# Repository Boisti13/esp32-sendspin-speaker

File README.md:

# ESP32 Sendspin Speaker

A network speaker for Home Assistant and Music Assistant on an ESP32-A1S
audio board. It plays [Sendspin](https://www.sendspin-audio.com/) streams
(Music Assistant's synchronised multi-room audio), shows what's playing on a
small colour screen and has hardware buttons for play/pause, volume and
tracks. Built with ESPHome.

> Since v0.2.0 it uses the Sendspin components built into ESPHome 2026.10;
> no pull requests or external components any more.

## Highlights

- **Sendspin player**: shows up in Music Assistant as a player and plays in
  sync with other Sendspin speakers.
- **ES8388 codec** on the A1S board, stereo, 48 kHz / 32-bit I²S; output
  set to both outputs (speaker and headphone) at boot, on the device itself.
- **Amplifier switched with playback**: on 150 ms after playback starts
  (no pop while the codec settles), off 300 ms after it stops or pauses (no
  click on the last audio).
- **1.47" screen** (320 × 172 landscape, ST7789V): play/pause icon, volume,
  IP address, title and artist. Long names end in "...", accented letters
  (ä, ö, ü, ß, é) are in the font. Redrawn only when something changes.
- **Rides out Wi-Fi gaps**: 2.5 MB of audio buffered ahead in PSRAM
  (Sendspin's default is 1 MB, about 5 s).
- **Diagnostics in Home Assistant**: Wi-Fi signal, uptime, free PSRAM and
  heap, and the reason for the last restart. A signal worse than about −70 dBm means dropouts: move the speaker
  or the access point, or use a board with an external antenna.
- **Five buttons that work without Home Assistant**: play/pause, previous,
  next, volume down/up go straight to the player and on to Music Assistant
  through Sendspin. Headphone jack detection.
- **Play picks up where you left off**: with nothing playing, even right
  after power-on, button 1 asks Music Assistant to play, and it resumes
  the speaker's queue with the last track.
- **Chime when it's online**: a short three-note chime when Wi-Fi first
  connects after power-on (not on later reconnects, and not over music).
  Built into the firmware. *Boot Sound* in Home Assistant turns it off;
  the setting survives restarts.

## Hardware

| Part | |
|---|---|
| Board | ESP32-A1S audio kit (ESP32-WROVER with PSRAM, ES8388 codec) |
| Codec | ES8388, I²C SDA 33 / SCL 32; I²S LRCLK 25, BCLK 27, DOUT 26, MCLK 0 |
| Amplifier enable | GPIO21 |
| Screen | Waveshare 1.47" 172 × 320, ST7789V; SPI CLK 14, MOSI 13, CS 15, DC 22, RST 12 |
| Headphone jack detect | GPIO39 |

### Buttons

| Button | Pin | Does | Entity in Home Assistant |
|---|---|---|---|
| 1 | GPIO36 | pause; when not playing, play (resumes Music Assistant's queue) | *Button 1 Play/Pause* |
| 2 | — | its pin (GPIO13) is the screen's MOSI | — |
| 3 | GPIO19 | previous track | *Button 3 Previous Track* |
| 4 | GPIO23 | next track | *Button 4 Next Track* |
| 5 | GPIO18 | volume down | *Button 5 Volume Down* |
| 6 | GPIO5 | volume up | *Button 6 Volume Up* |

The numbers are the ones printed on the board (KEY1–KEY6).

GPIO12 (screen reset) is a strapping pin: if it is high at power-on the
ESP32 picks 1.8 V flash and doesn't boot. Worth moving if boot is flaky.

### Custom PCB (in design)

A battery-powered board set of its own is being designed in KiCad in
[`hardware/`](hardware/README.md): a main board with the same ESP32-A1S
module, two 3 W amplifiers, a 1S LiPo charger and one USB-C port for
charging and flashing; a front panel with the screen (SPI like this one,
or an I²C OLED) and the buttons; a small USB-C board. Panel, USB-C,
battery, speakers, status LED, on/off switch and charge LEDs connect by
JST cable. It keeps the pins above, screen included, so it will get its
own `speaker-diy.yaml` with few changes. Not built yet.

## Install

| Step | |
|---|---|
| 1 | Copy `secrets.example.yaml` to `secrets.yaml` and fill in Wi-Fi, a new API key (`openssl rand -base64 32`) and an OTA password. In Home Assistant's ESPHome app the shared `secrets.yaml` gets `speaker_1_key` and `speaker_1_ota_password`. |
| 2 | Put `speaker.yaml`, `fonts/` and `sounds/` into the ESPHome folder. |
| 3 | Flash once over USB: `esphome run speaker.yaml`. After that, over Wi-Fi. |
| 4 | Add the device in Home Assistant with the API key. It needs no Home Assistant actions. |
| 5 | In Music Assistant, enable the Sendspin provider; the speaker appears as a player. |

## Example: playing an album

Start an album in Music Assistant on *Sendspin Media Player*. The board
switches to *playing*, waits 150 ms, turns the amplifier on and two seconds
later draws the screen once: pause icon, `VOL 65%`, the title in large type
and the artist below (*Die Ärzte* shows with its umlaut; a long title ends
in "..."). Press button 6 and the volume goes up a step; the screen redraws
with the new value. Press button 4 and Music Assistant skips to the next track.
Press button 1 to pause: the icon changes to play and the amplifier turns off
300 ms later.

## Layout

```
speaker.yaml           the whole device: board, codec, Sendspin, screen, buttons
requirements.txt       the ESPHome version it is tested with
fonts/                 Ubuntu Medium and Material Design Icons for the screen
sounds/boot.wav        the boot chime (1.5 s, 22 kHz mono)
scripts/make-boot-sound.py  makes sounds/boot.wav (synthesised, MIT like the rest)
secrets.example.yaml   the secrets the config expects
hardware/              KiCad 10 projects for the custom PCBs: main, front panel, USB-C (CERN-OHL-P-2.0)
```

## Development

- Check a change: `esphome config speaker.yaml`, then
  `esphome compile speaker.yaml`.
- ESPHome **2026.10.0** (`requirements.txt`), the version of Home
  Assistant's ESPHome app. Sendspin, `speaker_source` and `media_source`
  are built in since then; older versions don't have them.
- The screen has `update_interval: never`: every change that shows on it
  calls `component.update: tft_display`.
- Another boot sound: replace `sounds/boot.wav` (WAV, MP3, FLAC or Opus,
  short, ideally with ~300 ms of silence in front so the amplifier is on
  when it starts) or change and run `scripts/make-boot-sound.py`.

## License

MIT, see [LICENSE](LICENSE). The hardware in `hardware/` is under
CERN-OHL-P-2.0, see [hardware/LICENSE](hardware/LICENSE). Fonts: see
[THIRD_PARTY_NOTICES.md](THIRD_PARTY_NOTICES.md).

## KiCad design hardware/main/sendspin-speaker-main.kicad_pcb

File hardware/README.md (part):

# Custom PCB — Rev A (in design)

A battery-powered board set for the Sendspin speaker, replacing the
ESP32-Audio-Kit. It keeps the Audio Kit's pins wherever it can — the SPI
screen even stays on the same pins — so the firmware carries over as
`speaker-diy.yaml` with only the battery, charge and LED parts added.
KiCad 10 projects; the hardware is licensed under CERN-OHL-P-2.0
([LICENSE](LICENSE)), the firmware in the repo root under MIT.

> Status: all schematics drawn (ERC clean). **Main board placed, routed
> (Freerouting) and labelled**, DRC without errors, JLC files can be made.
> Front panel and USB-C board placed, not routed yet. Before ordering: check
> the NS4150B values and the part rotations (see *Open checks*). Nothing
> built or tested.

| Main board, 70 × 60 mm | Front panel, 75 × 45 mm | USB-C board, 32 × 22 mm |
|---|---|---|
|  |  |  |

Reference designators are numbered per sheet: MCU 1xx, Power 2xx, USB 3xx,
Audio 4xx, Connectors 5xx (front panel and USB-C board: 6xx, 7xx).

## Highlights

- **Three boards**: the main board with module, audio and power; a front
  panel with the display and the five buttons; a small USB-C board.
  Everything that sits in the enclosure wall — panel, USB-C, battery,
  speakers, status LED, on/off switch, charge LEDs — connects by JST cable,
  so the main board can go anywhere in the case.
- **USB-C either way**: on the main board directly, or on the USB-C board
  through a cable. Both footprints are on the main board; fit one.
- **SPI or I²C display**: the panel connector carries SCK/SCL, MOSI/SDA, CS
  and DC, so it takes the ST7789 the Audio Kit build uses (same pins), or
  an SSD1306/SH1106 OLED on the first two lines.
- **ESP32-A1S (Ai-Thinker, ES8388 version)**, the same module as the Audio
  Kit, hand-soldered (JLC doesn't stock it). Antenna over the board edge or
  a cutout; the footprint carries a copper keepout under it.
- **Stereo, 2 × 3 W**: two NS4150B in BTL into 4 Ω, powered straight from
  the battery, enabled together on GPIO21.
- **1S LiPo** with TP4056 charging (~500 mA, so any PC port works),
  DW01A + FS8205A protection, load sharing, red/green charge LEDs that the
  firmware can read too.
- **One USB-C port** for charging and flashing (CH340C with auto-reset).
- **On/off switch after the charger**: the battery still charges while the
  speaker is off.
- **0805 wherever possible** for resistors, capacitors and LEDs, so
  everything can be hand-soldered and reworked.

## Boards

| Board | KiCad project | Carries |
|---|---|---|
| Main | [`main/`](main/) | ESP32-A1S, amps, charger and protection, regulators, CH340C, Boot/Reset, on-board options for switch and charge LEDs, all connectors below |
| Front panel | [`ui/`](ui/) | buttons 1, 3, 4, 5, 6 and headers only (SPI and I²C display, status LED): any panel wiring can replace it |
| USB-C | [`usb/`](usb/) | USB-C receptacle only: any USB-C breakout or panel socket can replace it |

## Connectors (main board)

JST XH (2.5 mm) unless noted. Pin 1 first.

| Ref | To | Pins | Signals |
|---|---|---|---|
| J_UI | front panel | XH 12 | 3V3, GND, SCK/SCL (14), MOSI/SDA (13), CS (15), DC (22), BTN1 (36), BTN3 (19), BTN4 (23), BTN5 (18), BTN6 (5), LED (12, through R501 330 Ω) |
| J_USB | USB-C board | XH 6 | VBUS, D−, D+, CC1, CC2, GND |
| USB1 | — | USB-C 16-pin | the on-board option, in parallel with J_USB |
| J_BAT | LiPo cell | XH 2 | BAT+, BAT− |
| J_SW | on/off switch | XH 2 | VBAT_LS, VBAT_SW (switch in series) |
| J_CHG | charge LEDs | XH 3 | LED+ (VBUS), CHRG (red cathode), STDBY (green cathode) |
| J_LED | status LED | XH 3 | VBAT_SW, LED (12) through 330 Ω, GND |
| J_SPK_L | left speaker | XH 2 | OUTP, OUTN |
| J_SPK_R | right speaker | XH 2 | OUTP, OUTN |

- **Speakers are bridged (BTL)**: neither wire is ground. Never tie a
  speaker wire to GND or share a return between the two speakers.
- **Battery on JST XH** like every other cable: most cells ship with a PH
  plug, so crimp an XH plug on (or use an adapter lead). Cells differ in
  polarity: check before plugging in. Silkscreen `+`/`−` at the connector.
- **J_UI**: a SPI display uses all four display lines; an I²C OLED only
  SCK/SCL and MOSI/SDA, with the two 4.7 kΩ pull-ups on the main board
  fitted (leave them off for SPI). GPIO36's 10 kΩ pull-up is on the main
  board too, so the panel has nothing but buttons to GND and headers.
  Keep the cable short (≤ 20 cm). The LED pin is GPIO12 after R501
  (330 Ω), so a panel LED wires straight on.
- **J_USB / USB1**: the 5.1 kΩ CC resistors (R301/R302) and the USBLC6-2SC6
  are on the main board and serve both, so the off-board side is a bare
  receptacle: our USB-C board or any breakout that brings out VBUS, D−, D+,
  CC1, CC2 and GND (leave R301/R302 off if it has its own 5.1 kΩ). Fit
  either USB1 or J_USB, not both. The cable carries charge and
  load current (amps on battery through load sharing), so XH's 3 A per pin
  is plenty; keep it short (≤ 15 cm) for USB full speed.
- **J_SW**: the switch goes in series between load sharing and VBAT_SW.
  Fit either the on-board MSK12C02 or J_SW with a panel switch; with
  neither, bridge the solder jumper next to them.
- **J_CHG**: the LED resistors stay on the main board; the on-board 0805
  LEDs are in parallel and can be left off.
- **J_LED**: GPIO12 goes out through R501 (330 Ω), so a plain LED wires
  straight to LED/GND; VBAT_SW is there for an SK6812-type LED (needs
  > 3.7 V, hence not 3V3; R501 is its data series resistor). The on-board
  LED (D101/R108) stays as well.

## Parts and footprints

Footprints are set on the symbol the moment it is placed. KiCad's own
library where it has the part; otherwise imported from LCSC into
`lib/lcsc` (see [Libraries](#libraries)).

| Block | Part | Footprint | LCSC |
|---|---|---|---|
| Module | ESP32-A1S (ES8388), hand-soldered | `lcsc:WIRELM-SMD_ESP32-A1S` (+ antenna keepout) | C277945 |
| Amps | 2 × NS4150B | `lcsc:MSOP-8_L3.0-W3.0-P0.65-LS5.0-BL` | C189961 |
| Bulk | 470 µF, ≥ 6.3 V | `Capacitor_SMD:CP_Elec_8x10` | |
| Charger | TP4056 | `Package_SO:SOIC-8-1EP_3.9x4.9mm_P1.27mm_EP2.41x3.3mm` | |
| Protection | DW01A | `Package_TO_SOT_SMD:SOT-23-6` | |
| | FS8205A | `lcsc:SOT-23-6_L2.9-W1.6-P0.95-LS2.8-BR` | C2830320 |
| Load sharing | AO3401A | `Package_TO_SOT_SMD:SOT-23` | |
| | SS34 | `Diode_SMD:D_SMA` | |
| Power switch | MSK12C02 | `lcsc:SW-TH_MSK12C02` | C431540 |
| Switch bypass | solder jumper JP201 | `Jumper:SolderJumper-2_P1.3mm_Open_RoundedPad1.0x1.5mm` | |
| Charge status | 2 × BAT54W (GPIO isolation) | `Package_TO_SOT_SMD:SOT-323_SC-70` | |
| 3.3 V | AP2112K-3.3 | `Package_TO_SOT_SMD:SOT-23-5` | |
| 3.3 V (CH340C) | XC6206P332MR | `Package_TO_SOT_SMD:SOT-23-3` | |
| USB-UART | CH340C | `Package_SO:SOIC-16_3.9x9.9mm_P1.27mm` | |
| Auto-reset | UMH3N | `Package_TO_SOT_SMD:SOT-363_SC-70-6` | |
| ESD | USBLC6-2SC6 | `Package_TO_SOT_SMD:SOT-23-6` | |
| USB-C | 16-pin receptacle | `Connector_USB:USB_C_Receptacle_HRO_TYPE-C-31-M-12` | |
| Boot, Reset | tactile 5.1 × 5.1 mm | `Button_Switch_SMD:SW_Push_1P1T_XKB_TS-1187A` | |
| Panel buttons | tactile 6 × 6 mm THT | `Button_Switch_THT:SW_PUSH_6mm` | |
| Display headers | 1 × 8 (SPI), 1 × 4 (I²C) | `Connector_PinHeader_2.54mm:PinHeader_1x08/1x04_P2.54mm_Vertical` | |
| JST XH | B*B-XH-A vertical | `Connector_JST:JST_XH_B<n>B-XH-A_1x<n>_P2.50mm_Vertical` | |
| R, C, LED | | `Resistor_SMD:R_0805_2012Metric`, `Capacitor_SMD:C_0805_2012Metric`, `LED_SMD:LED_0805_2012Metric` | |

LCSC numbers for the KiCad-library parts are filled in when they go into
the schematic (field `LCSC`), for JLC assembly.

**0805** for resistors, capacitors and LEDs wherever the part exists in
it. Exceptions: the bulk capacitor, and values that don't come in 0805 at
the needed voltage (check 22 µF for ≥ 10 V rating and DC-bias derating).

**Values and wiring notes**

- TP4056: R_PROG 2.4 kΩ (~500 mA). CHRG/STDBY reach GPIO4/GPIO2 through
  BAT54W diodes (cathode at the TP4056): the LEDs hang off VBUS, and without
  the diodes 5 V would leak into the GPIOs — and GPIO2 high at reset would
  stop USB flashing.
- CH340C: own XC6206 3.3 V from VBUS (USB only, no battery drain), V3 tied
  to VCC, TX/RX through 470 Ω. Auto-reset DTR/RTS → EN/GPIO0; EN 10 kΩ
  pull-up + 1 µF. GPIO0 is also the codec's MCLK, as on the Audio Kit.
- USB-C: 5.1 kΩ on CC1 and CC2 separately; A6/B6 and A7/B7 tied.
- Module: 22 µF + 100 nF at 3V3.
- NS4150B: inputs from the module's differential speaker outputs through
  100 nF + 100 kΩ per leg (gain = 240 kΩ / Rin = 2.4, −3 dB at 16 Hz; 47 kΩ
  gives 5.1 if it's too quiet), Bypass 1 µF, supply 10 µF + 1 µF (the
  datasheet's 1 µF instead of 100 nF), R421 100 kΩ pull-down on AMP_EN so
  the amps stay off while booting.
- No headphone output (owner, 2026-10-30): the module's HPOUTL/R are left
  open; GPIO39 (the Audio Kit's headphone detect) keeps its 10 kΩ pull-up
  and is spare.
- Front panel: no parts besides buttons and headers. ST7789 RST tied to
  3.3 V (the driver sends a software reset), backlight always on; J604
  takes a status LED directly.
- Battery sense: 2 × 470 kΩ + 100 nF on the **cell** (VBAT) → GPIO34, ~4.5 µA.
  Not on VBAT_SW: with USB in, load sharing puts ~4.6 V from VBUS there and
  the cell couldn't be measured while charging.
- Protection sits in the negative lead: BAT_N is the cell's minus, GND
  the protected system ground (P−). DW01A: 100 Ω / 100 nF supply, CS via 1 kΩ.
- Load sharing: SS34 from VBUS to the load (VBAT_LS); AO3401A with drain
  at the cell, source at the load, gate on VBUS (100 kΩ to GND), so it
  connects the cell only without USB.
- AP2112K-3.3: 10 µF in and out, EN tied to VIN.
- Flashing over USB needs the switch on.

## Open checks

- **NS4150B values**: Rin/Cin from the gain formula; the typical
  application page of the datasheet wasn't readable either — compare.
- **Part rotations** in JLC's placement preview: KiCad and JLC disagree on
  some footprints' zero orientation (SOT-23, SOIC, USB-C).

## Pin plan

The ESP32-A1S keeps the codec's I²C (GPIO32/33) and I²S (25/26/27/35)
inside the module; they are not on its pads. The free pads are GPIO 0, 2,
4, 5, 12, 13, 14, 15, 18, 19, 21, 22, 23, 34, 36, 39 and TX/RX.

| Function | GPIO | Same as Audio Kit? |
|---|---|---|
| Codec I²C / I²S | 32/33, 25/26/27/35 + MCLK 0 | yes, inside the module |
| Display SCK/SCL, MOSI/SDA, CS, DC | 14, 13, 15, 22 | yes (the ST7789's pins; its reset on 12 is dropped) |
| Amp enable | 21 | yes |
| Buttons 1 play/pause, 3 prev, 4 next, 5 vol −, 6 vol + | 36, 19, 23, 18, 5 | yes; 36 needs an external 10 kΩ pull-up |
| Spare (was headphone detect) | 39 | 10 kΩ pull-up kept; input only |
| Status LED | 12 | new; 10 kΩ pull-down keeps the strap low at boot |
| CHRG / STDBY | 4 / 2 | new; through BAT54W, internal pull-ups |
| Battery ADC | 34 | new |
| UART (CH340C) | 1 / 3 | yes |

Strapping pins: GPIO12 must be low at reset (else 1.8 V flash, no boot),
GPIO2 low or floating for USB flashing, GPIO15 high (CS's pull-up keeps it
so). All pads are in use.

## Firmware changes (`speaker-diy.yaml`, later)

- Display: keep the ST7789 config without `reset_pin`, or switch to
  `ssd1306_i2c` with `i2c: sda: 13, scl: 14` (a second bus; the codec's
  stays on 33/32) and a monochrome UI.
- Battery `adc` on GPIO34 (12 dB, ×2, cell voltage); warn below 3.5 V (LDO).
- Status LED on GPIO12.
- *Charging* / *Charged* binary sensors on GPIO4/GPIO2 (pull-up): charging =
  CHRG low and STDBY high, charged = STDBY low and CHRG high; anything else
  means no USB (without VBUS both can read low through the TP4056).

## Libraries

- KiCad 10's standard libraries for everything they have.
- `lib/lcsc.*`: the five parts KiCad doesn't have, imported from LCSC's
  EasyEDA library with [easyeda2kicad](https://github.com/uPesy/easyeda2kicad.py)
  (symbol, footprint, STEP model). Afterwards: 3D paths point at
  `${KIPRJMOD}/../lib/lcsc.3dshapes/`, the locating pegs of MSK12C02 and
  PJ-320D are non-plated, the A1S got an antenna keepout and a courtyard
  around its pads, the PJ-320D a courtyard (it had none) and its 3D model
  moved 7.6 mm onto its pads, and MSK12C02 is marked SMD. Check every
  imported part's courtyard and 3D model before using it.
  See [THIRD_PARTY_NOTICES.md](../THIRD_PARTY_NOTICES.md).
- `lib/sendspin-speaker.*`: parts we draw ourselves (none yet).

To import another part: `easyeda2kicad --full --lcsc_id C… --output
<scratch>/lcsc`, check it, then merge it into `lib/lcsc.*` with the same
fixes.

## Layout

```
main/sendspin-speaker-main.kicad_*   main board; the top sheet is the block diagram
main/usb.kicad_sch                   USB-C, ESD, CH340C, auto-reset
main/power.kicad_sch                 charger, protection, load sharing, switch, 3V3, battery sense
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
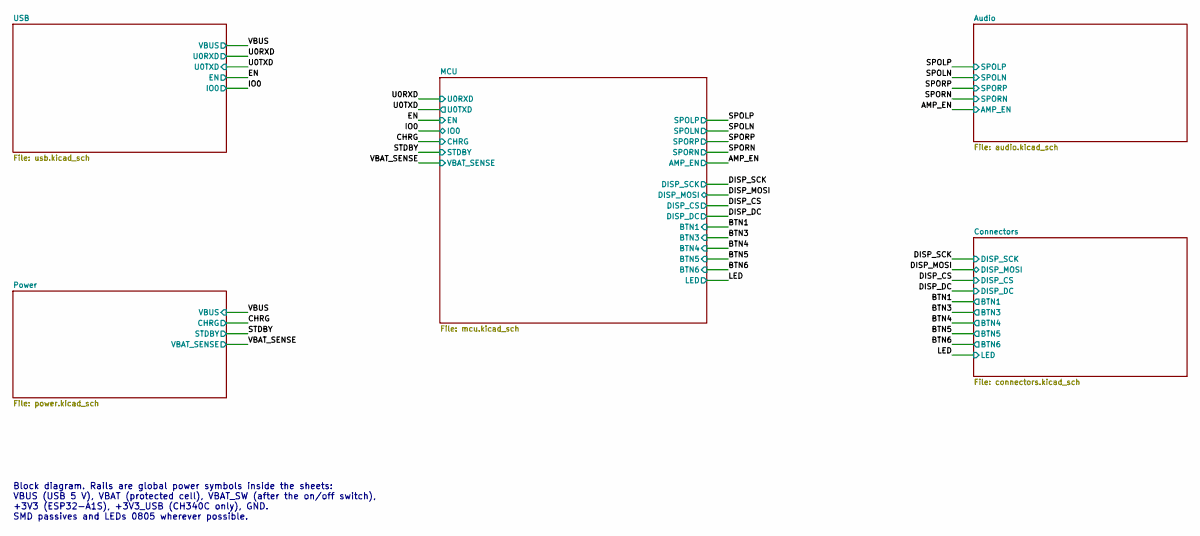
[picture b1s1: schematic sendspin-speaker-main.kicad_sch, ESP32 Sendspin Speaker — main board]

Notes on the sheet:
Block diagram. Rails are global power symbols inside the sheets: VBUS (USB 5 V), VBAT (protected cell), VBAT_SW (after the on/off switch), +3V3 (ESP32-A1S), +3V3_USB (CH340C only), GND. SMD passives and LEDs 0805 wherever possible.

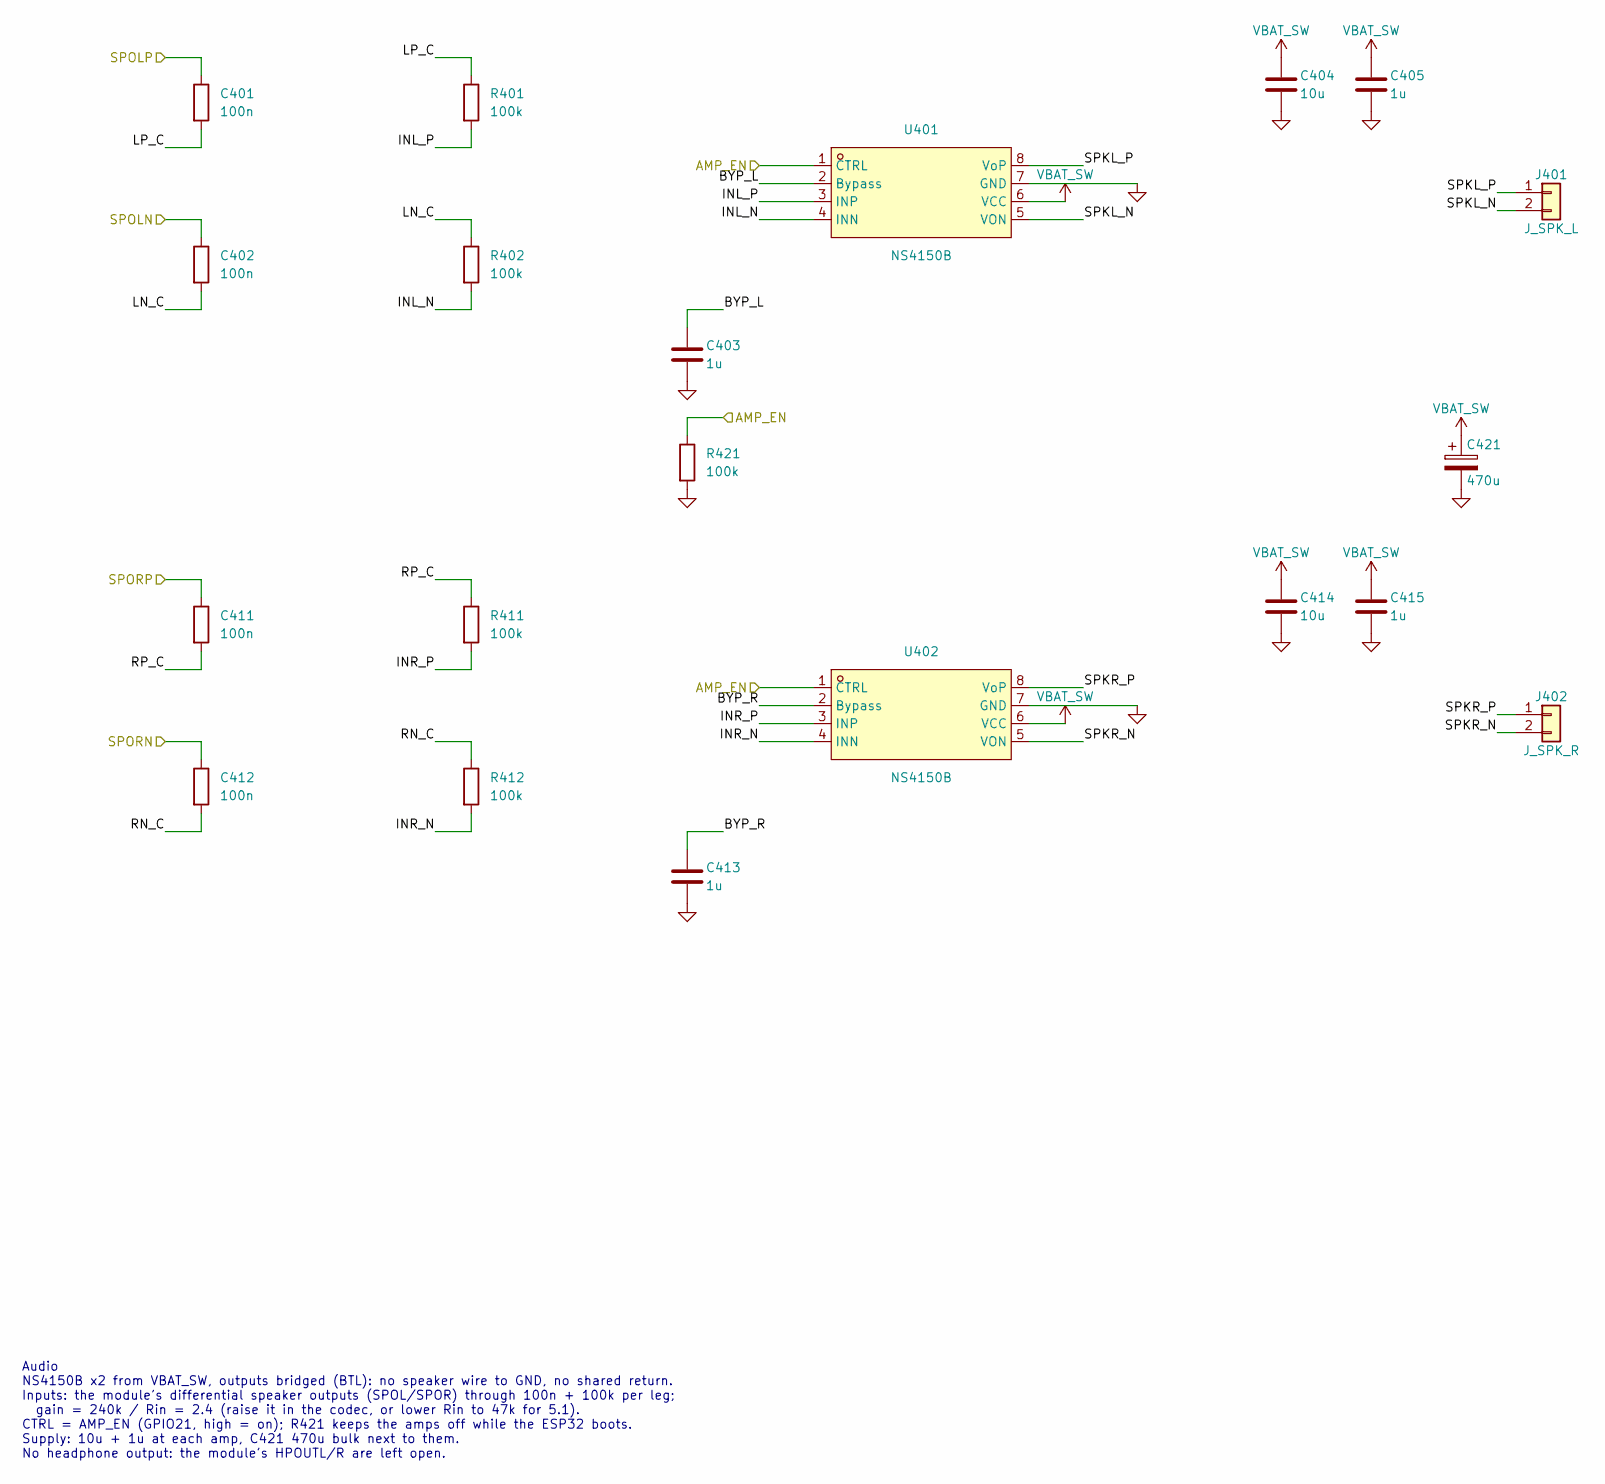
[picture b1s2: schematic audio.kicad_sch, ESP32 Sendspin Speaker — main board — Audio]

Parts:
C401, C402, C411, C412: 100n; C_0805_2012Metric; LCSC C49678
C403, C405, C413, C415: 1u; C_0805_2012Metric; LCSC C28323
C404, C414: 10u; C_0805_2012Metric; LCSC C15850
C421: 470u; CP_Elec_8x10; LCSC C249545
J401: J_SPK_L; JST_XH_B2B-XH-A_1x02_P2.50mm_Vertical
J402: J_SPK_R; JST_XH_B2B-XH-A_1x02_P2.50mm_Vertical
R401, R402, R411, R412, R421: 100k; R_0805_2012Metric; LCSC C149504
U401, U402: NS4150B; MSOP-8_L3.0-W3.0-P0.65-LS5.0-BL; LCSC C189961

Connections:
/AMP_EN: R421.1, U401.1 (CTRL), U402.1 (CTRL); also elsewhere on the board
/Audio/BYP_L: C403.1, U401.2 (Bypass)
/Audio/BYP_R: C413.1, U402.2 (Bypass)
/Audio/INL_N: R402.2, U401.4 (INN)
/Audio/INL_P: R401.2, U401.3 (INP)
/Audio/INR_N: R412.2, U402.4 (INN)
/Audio/INR_P: R411.2, U402.3 (INP)
/Audio/LN_C: C402.2, R402.1
/Audio/LP_C: C401.2, R401.1
/Audio/RN_C: C412.2, R412.1
/Audio/RP_C: C411.2, R411.1
/Audio/SPKL_N: J401.2, U401.5 (VON)
/Audio/SPKL_P: J401.1, U401.8 (VoP)
/Audio/SPKR_N: J402.2, U402.5 (VON)
/Audio/SPKR_P: J402.1, U402.8 (VoP)
/SPOLN: C402.1; also elsewhere on the board
/SPOLP: C401.1; also elsewhere on the board
/SPORN: C412.1; also elsewhere on the board
/SPORP: C411.1; also elsewhere on the board
GND: C403.2, C404.2, C405.2, C413.2, C414.2, C415.2, C421.2, R421.2, U401.7 (GND), U402.7 (GND); also elsewhere on the board
VBAT_SW: C404.1, C405.1, C414.1, C415.1, C421.1, U401.6 (VCC), U402.6 (VCC); also elsewhere on the board

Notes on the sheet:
Audio NS4150B x2 from VBAT_SW, outputs bridged (BTL): no speaker wire to GND, no shared return. Inputs: the module's differential speaker outputs (SPOL/SPOR) through 100n + 100k per leg; gain = 240k / Rin = 2.4 (raise it in the codec, or lower Rin to 47k for 5.1). CTRL = AMP_EN (GPIO21, high = on);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

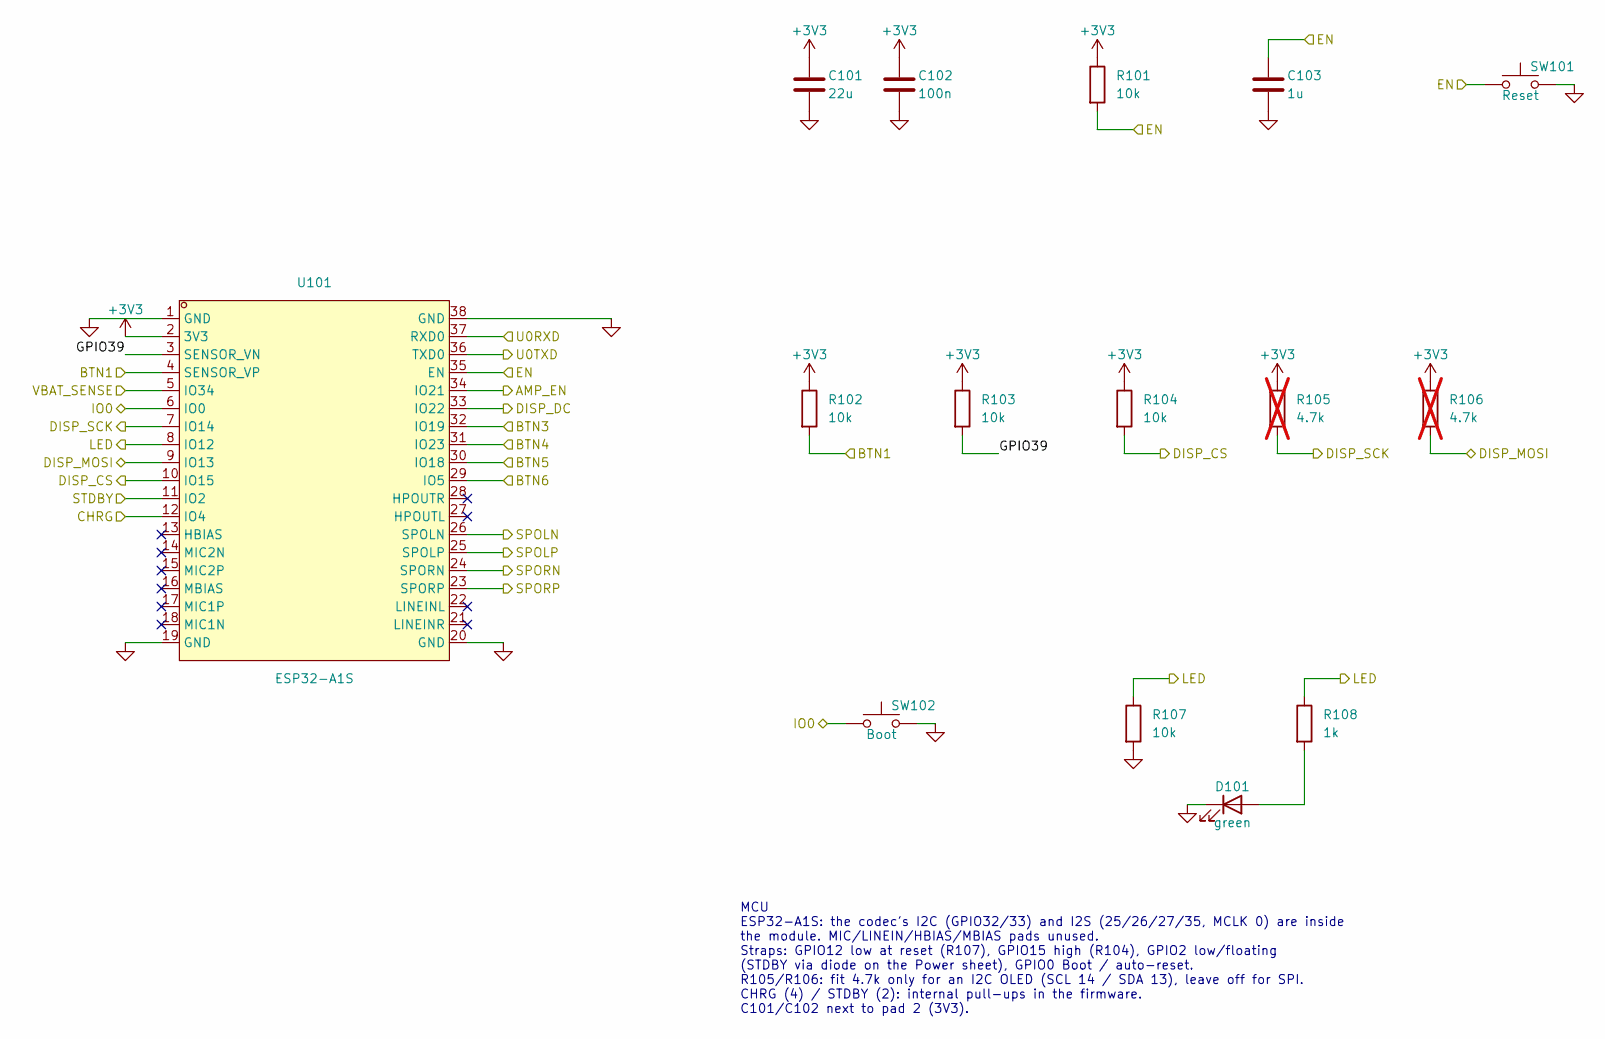
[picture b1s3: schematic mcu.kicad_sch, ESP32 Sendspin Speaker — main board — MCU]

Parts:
C101: 22u; C_0805_2012Metric; LCSC C45783
C102: 100n; C_0805_2012Metric; LCSC C49678
C103: 1u; C_0805_2012Metric; LCSC C28323
D101: green; LED_0805_2012Metric; LCSC C2297
R101, R102, R103, R104, R107: 10k; R_0805_2012Metric; LCSC C17414
R105, R106: 4.7k; R_0805_2012Metric; LCSC C17673; not fitted
R108: 1k; R_0805_2012Metric; LCSC C17513
SW101: Reset; SW_Push_1P1T_XKB_TS-1187A; LCSC C318884
SW102: Boot; SW_Push_1P1T_XKB_TS-1187A; LCSC C318884
U101: ESP32-A1S; WIRELM-SMD_ESP32-A1S; LCSC C277945

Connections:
+3V3: C101.1, C102.1, R101.1, R102.1, R103.1, R104.1, R105.1, R106.1, U101.2 (3V3); also elsewhere on the board
/AMP_EN: U101.34 (IO21); also elsewhere on the board
/BTN1: R102.2, U101.4 (SENSOR_VP); also elsewhere on the board
/BTN3: U101.32 (IO19); also elsewhere on the board
/BTN4: U101.31 (IO23); also elsewhere on the board
/BTN5: U101.30 (IO18); also elsewhere on the board
/BTN6: U101.29 (IO5); also elsewhere on the board
/CHRG: U101.12 (IO4); also elsewhere on the board
/DISP_CS: R104.2, U101.10 (IO15); also elsewhere on the board
/DISP_DC: U101.33 (IO22); also elsewhere on the board
/DISP_MOSI: R106.2, U101.9 (IO13); also elsewhere on the board
/DISP_SCK: R105.2, U101.7 (IO14); also elsewhere on the board
/EN: C103.1, R101.2, SW101.1, U101.35 (EN); also elsewhere on the board
/IO0: SW102.1, U101.6 (IO0); also elsewhere on the board
/LED: R107.1, R108.1, U101.8 (IO12); also elsewhere on the board
/MCU/GPIO39: R103.2, U101.3 (SENSOR_VN)
/SPOLN: U101.26 (SPOLN); also elsewhere on the board
/SPOLP: U101.25 (SPOLP); also elsewhere on the board
/SPORN: U101.24 (SPORN); also elsewhere on the board
/SPORP: U101.23 (SPORP); also elsewhere on the board
/STDBY: U101.11 (IO2); also elsewhere on the board
/U0RXD: U101.37 (RXD0); also elsewhere on the board
/U0TXD: U101.36 (TXD0); also elsewhere on the board
/VBAT_SENSE: U101.5 (IO34); also elsewhere on the board
GND: C101.2, C102.2, C103.2, D101.1 (K), R107.2, SW101.2, SW102.2, U101.1 (GND), U101.19 (GND), U101.20 (GND), U101.38 (GND); also elsewhere on the board
unnamed: D101.2 (A), R108.2

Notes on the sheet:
MCU ESP32-A1S: the codec's I2C (GPIO32/33) and I2S (25/26/27/35, MCLK 0) are inside the module. MIC/LINEIN/HBIAS/MBIAS pads unused. Straps: GPIO12 low at reset (R107), GPIO15 high (R104), GPIO2 low/floating (STDBY via diode on the Power sheet), GPIO0 Boot / auto-reset. R105/R106: fit 4.7k only for 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

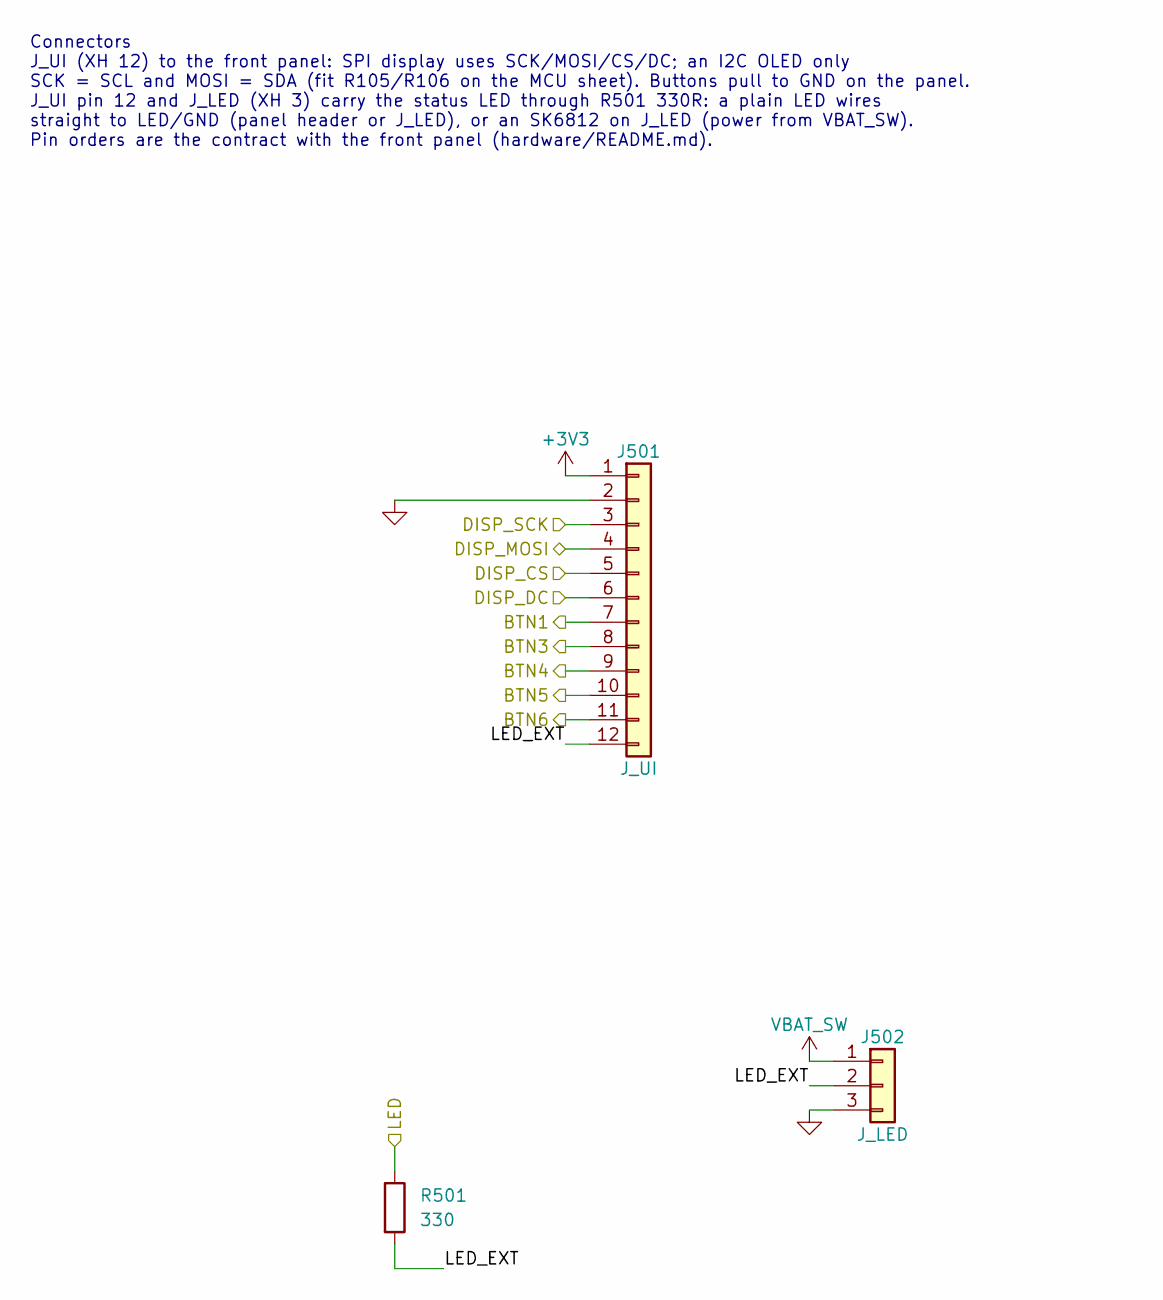
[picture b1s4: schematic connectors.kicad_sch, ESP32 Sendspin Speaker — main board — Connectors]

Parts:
J501: J_UI; JST_XH_B12B-XH-A_1x12_P2.50mm_Vertical
J502: J_LED; JST_XH_B3B-XH-A_1x03_P2.50mm_Vertical
R501: 330; R_0805_2012Metric; LCSC C17630

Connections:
+3V3: J501.1; also elsewhere on the board
/BTN1: J501.7; also elsewhere on the board
/BTN3: J501.8; also elsewhere on the board
/BTN4: J501.9; also elsewhere on the board
/BTN5: J501.10; also elsewhere on the board
/BTN6: J501.11; also elsewhere on the board
/Connectors/LED_EXT: J501.12, J502.2, R501.2
/DISP_CS: J501.5; also elsewhere on the board
/DISP_DC: J501.6; also elsewhere on the board
/DISP_MOSI: J501.4; also elsewhere on the board
/DISP_SCK: J501.3; also elsewhere on the board
/LED: R501.1; also elsewhere on the board
GND: J501.2, J502.3; also elsewhere on the board
VBAT_SW: J502.1; also elsewhere on the board

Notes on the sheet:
Connectors J_UI (XH 12) to the front panel: SPI display uses SCK/MOSI/CS/DC; an I2C OLED only SCK = SCL and MOSI = SDA (fit R105/R106 on the MCU sheet). Buttons pull to GND on the panel. J_UI pin 12 and J_LED (XH 3) carry the status LED through R501 330R: a plain LED wires straight to LED/GND (pane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

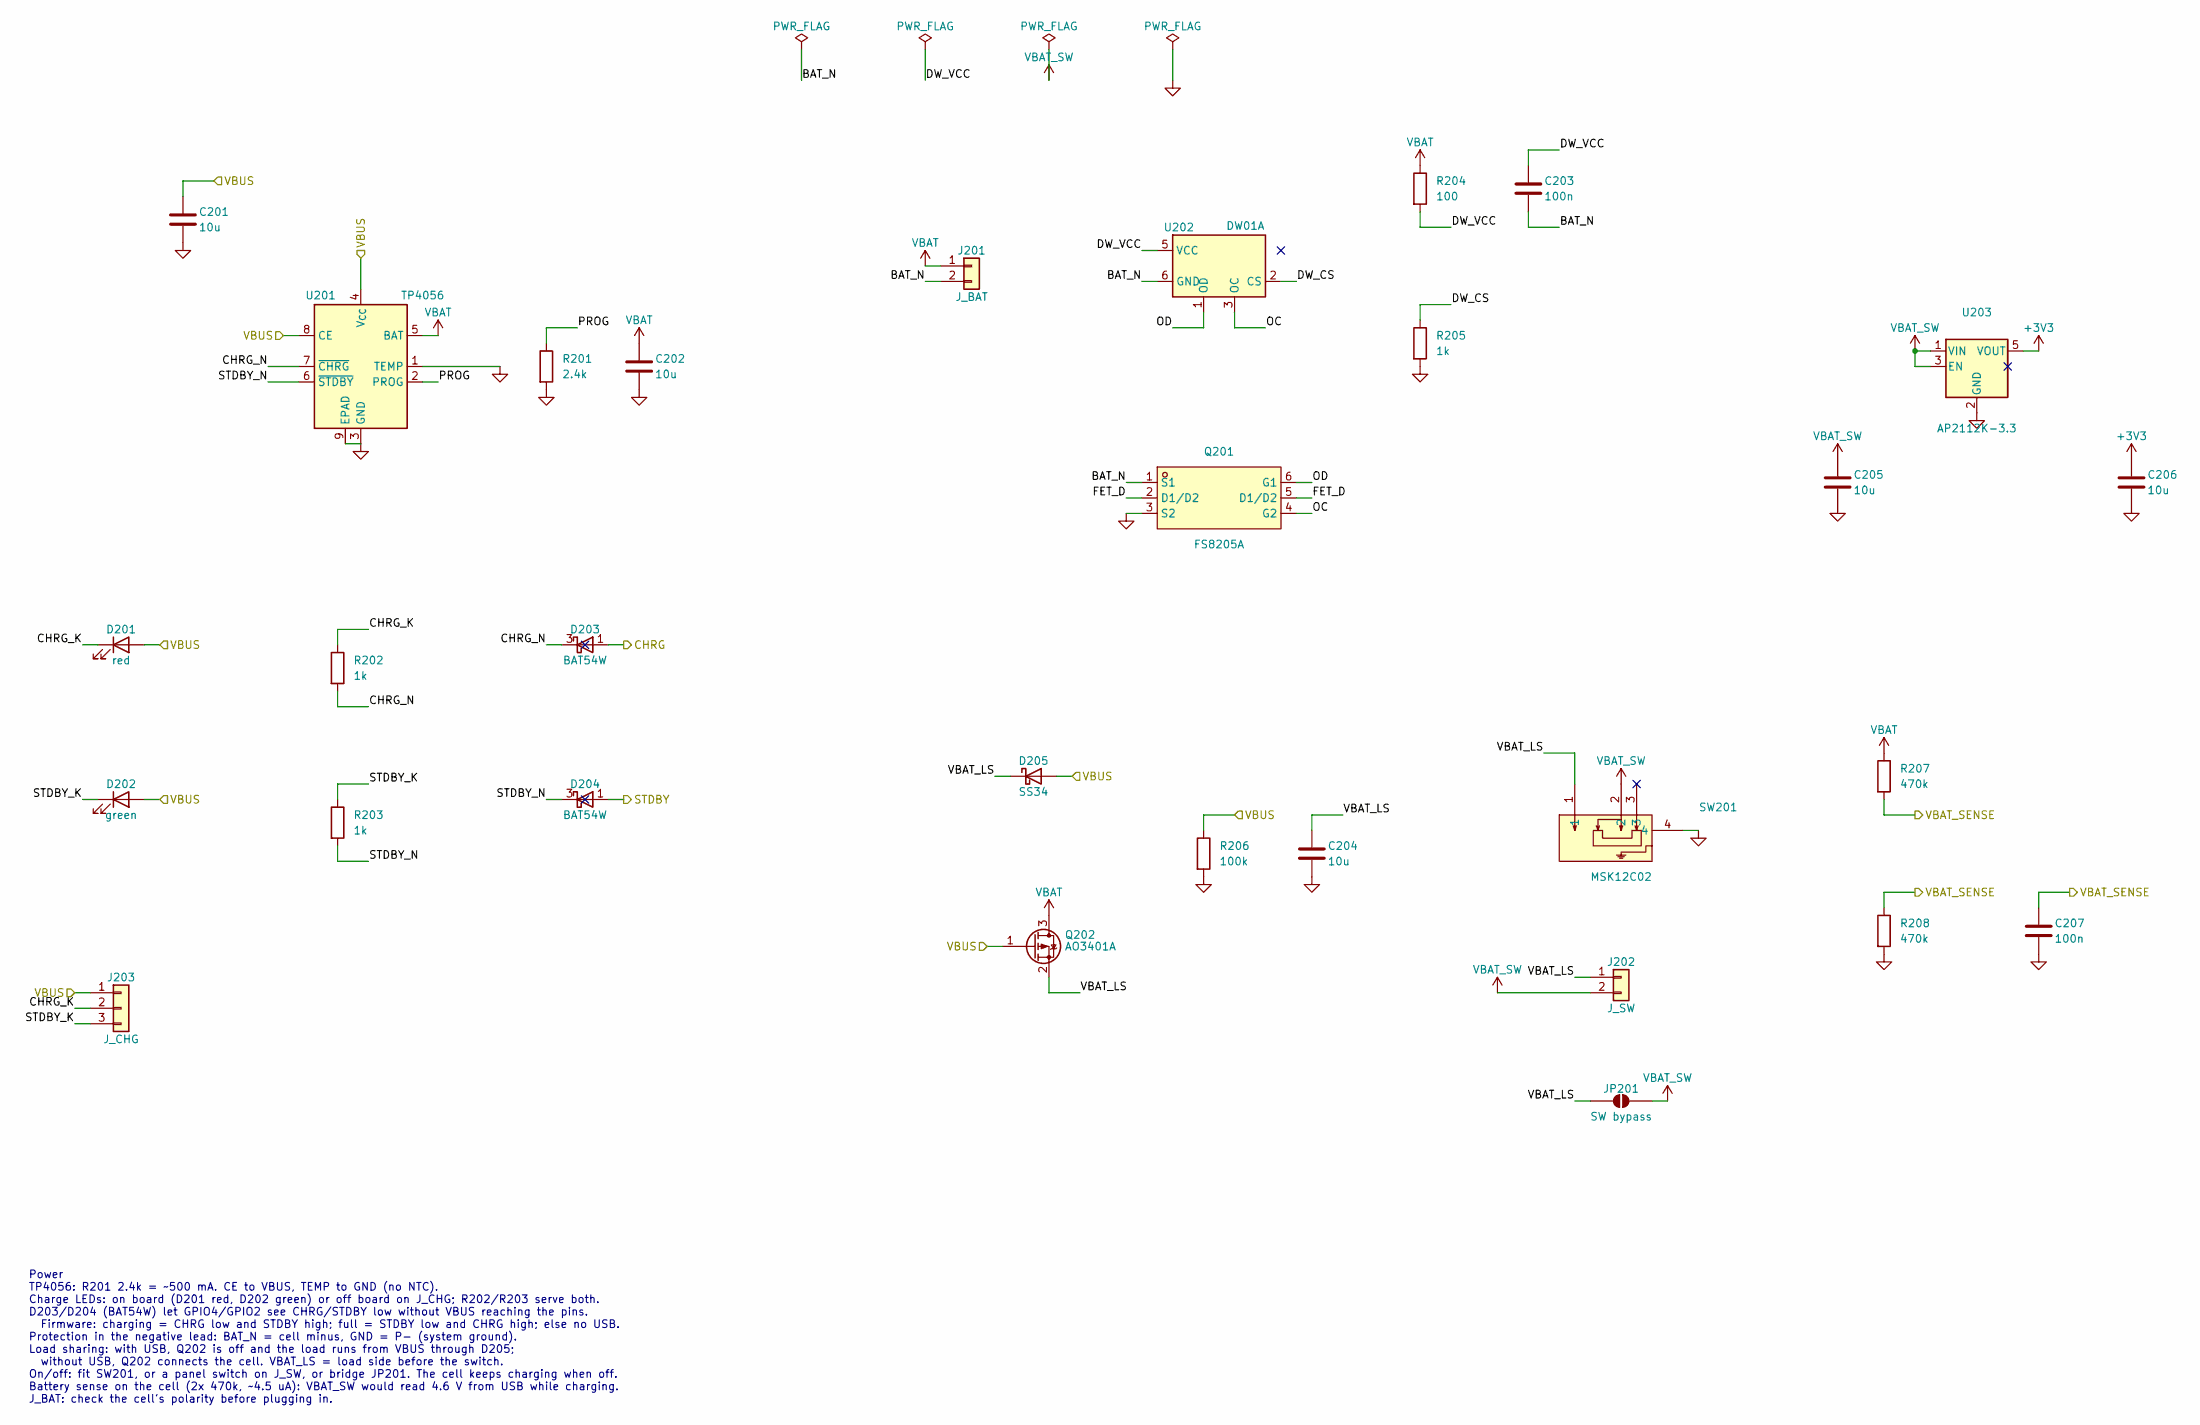
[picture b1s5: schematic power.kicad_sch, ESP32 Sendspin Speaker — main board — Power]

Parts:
C201, C202, C204, C205, C206: 10u; C_0805_2012Metric; LCSC C15850
C203, C207: 100n; C_0805_2012Metric; LCSC C49678
D201: red; LED_0805_2012Metric; LCSC C84256
D202: green; LED_0805_2012Metric; LCSC C2297
D203, D204: BAT54W; SOT-323_SC-70; LCSC C2992467
D205: SS34; D_SMA; LCSC C8678
J201: J_BAT; JST_XH_B2B-XH-A_1x02_P2.50mm_Vertical
J202: J_SW; JST_XH_B2B-XH-A_1x02_P2.50mm_Vertical
J203: J_CHG; JST_XH_B3B-XH-A_1x03_P2.50mm_Vertical
JP201: SW bypass; SolderJumper-2_P1.3mm_Open_RoundedPad1.0x1.5mm
Q201: FS8205A; SOT-23-6_L2.9-W1.6-P0.95-LS2.8-BR; LCSC C2830320
Q202: AO3401A; SOT-23; LCSC C15127
R201: 2.4k; R_0805_2012Metric; LCSC C17526
R202, R203, R205: 1k; R_0805_2012Metric; LCSC C17513
R204: 100; R_0805_2012Metric; LCSC C17408
R206: 100k; R_0805_2012Metric; LCSC C149504
R207, R208: 470k; R_0805_2012Metric; LCSC C17709
SW201: MSK12C02; SW-TH_MSK12C02; LCSC C431540
U201: TP4056; SOIC-8-1EP_3.9x4.9mm_P1.27mm_EP2.41x3.3mm; LCSC C16581
U202: DW01A; SOT-23-6; LCSC C351410
U203: AP2112K-3.3; SOT-23-5; LCSC C51118

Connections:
+3V3: C206.1, U203.5 (VOUT); also elsewhere on the board
/CHRG: D203.1 (A); also elsewhere on the board
/Power/BAT_N: C203.2, J201.2, Q201.1 (S1), U202.6 (GND)
/Power/CHRG_K: D201.1 (K), J203.2, R202.1
/Power/CHRG_N: D203.3 (K), R202.2, U201.7 (~CHRG)
/Power/DW_CS: R205.1, U202.2 (CS)
/Power/DW_VCC: C203.1, R204.2, U202.5 (VCC)
/Power/FET_D: Q201.2 (D1/D2), Q201.5 (D1/D2)
/Power/OC: Q201.4 (G2), U202.3 (OC)
/Power/OD: Q201.6 (G1), U202.1 (OD)
/Power/PROG: R201.1, U201.2 (PROG)
/Power/STDBY_K: D202.1 (K), J203.3, R203.1
/Power/STDBY_N: D204.3 (K), R203.2, U201.6 (~STDBY)
/Power/VBAT_LS: C204.1, D205.1 (K), J202.1, JP201.1 (A), Q202.2 (S), SW201.1
/STDBY: D204.1 (A); also elsewhere on the board
/VBAT_SENSE: C207.1, R207.2, R208.1; also elsewhere on the board
/VBUS: C201.1, D201.2 (A), D202.2 (A), D205.2 (A), J203.1, Q202.1 (G), R206.1, U201.4 (V_{CC}), U201.8 (CE); also elsewhere on the board
GND: C201.2, C202.2, C204.2, C205.2, C206.2, C207.2, Q201.3 (S2), R201.2, R205.2, R206.2, R208.2, SW201.4, U201.1 (TEMP), U201.3 (GND), U201.9 (EPAD), U203.2 (GND); also elsewhere on the board
VBAT: C202.1, J201.1, Q202.3 (D), R204.1, R207.1, U201.5 (BAT)
VBAT_SW: C205.1, J202.2, JP201.2 (B), SW201.2, U203.1 (VIN), U203.3 (EN); also elsewhere on the board

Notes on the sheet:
Power TP4056: R201 2.4k = ~500 mA. CE to VBUS, TEMP to GND (no NTC). Charge LEDs: on board (D201 red, D202 green) or off board on J_CHG; R202/R203 serve both. D203/D204 (BAT54W) let GPIO4/GPIO2 see CHRG/STDBY low without VBUS reaching the pins. Firmware: charging = CHRG low and STDBY high; full = S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

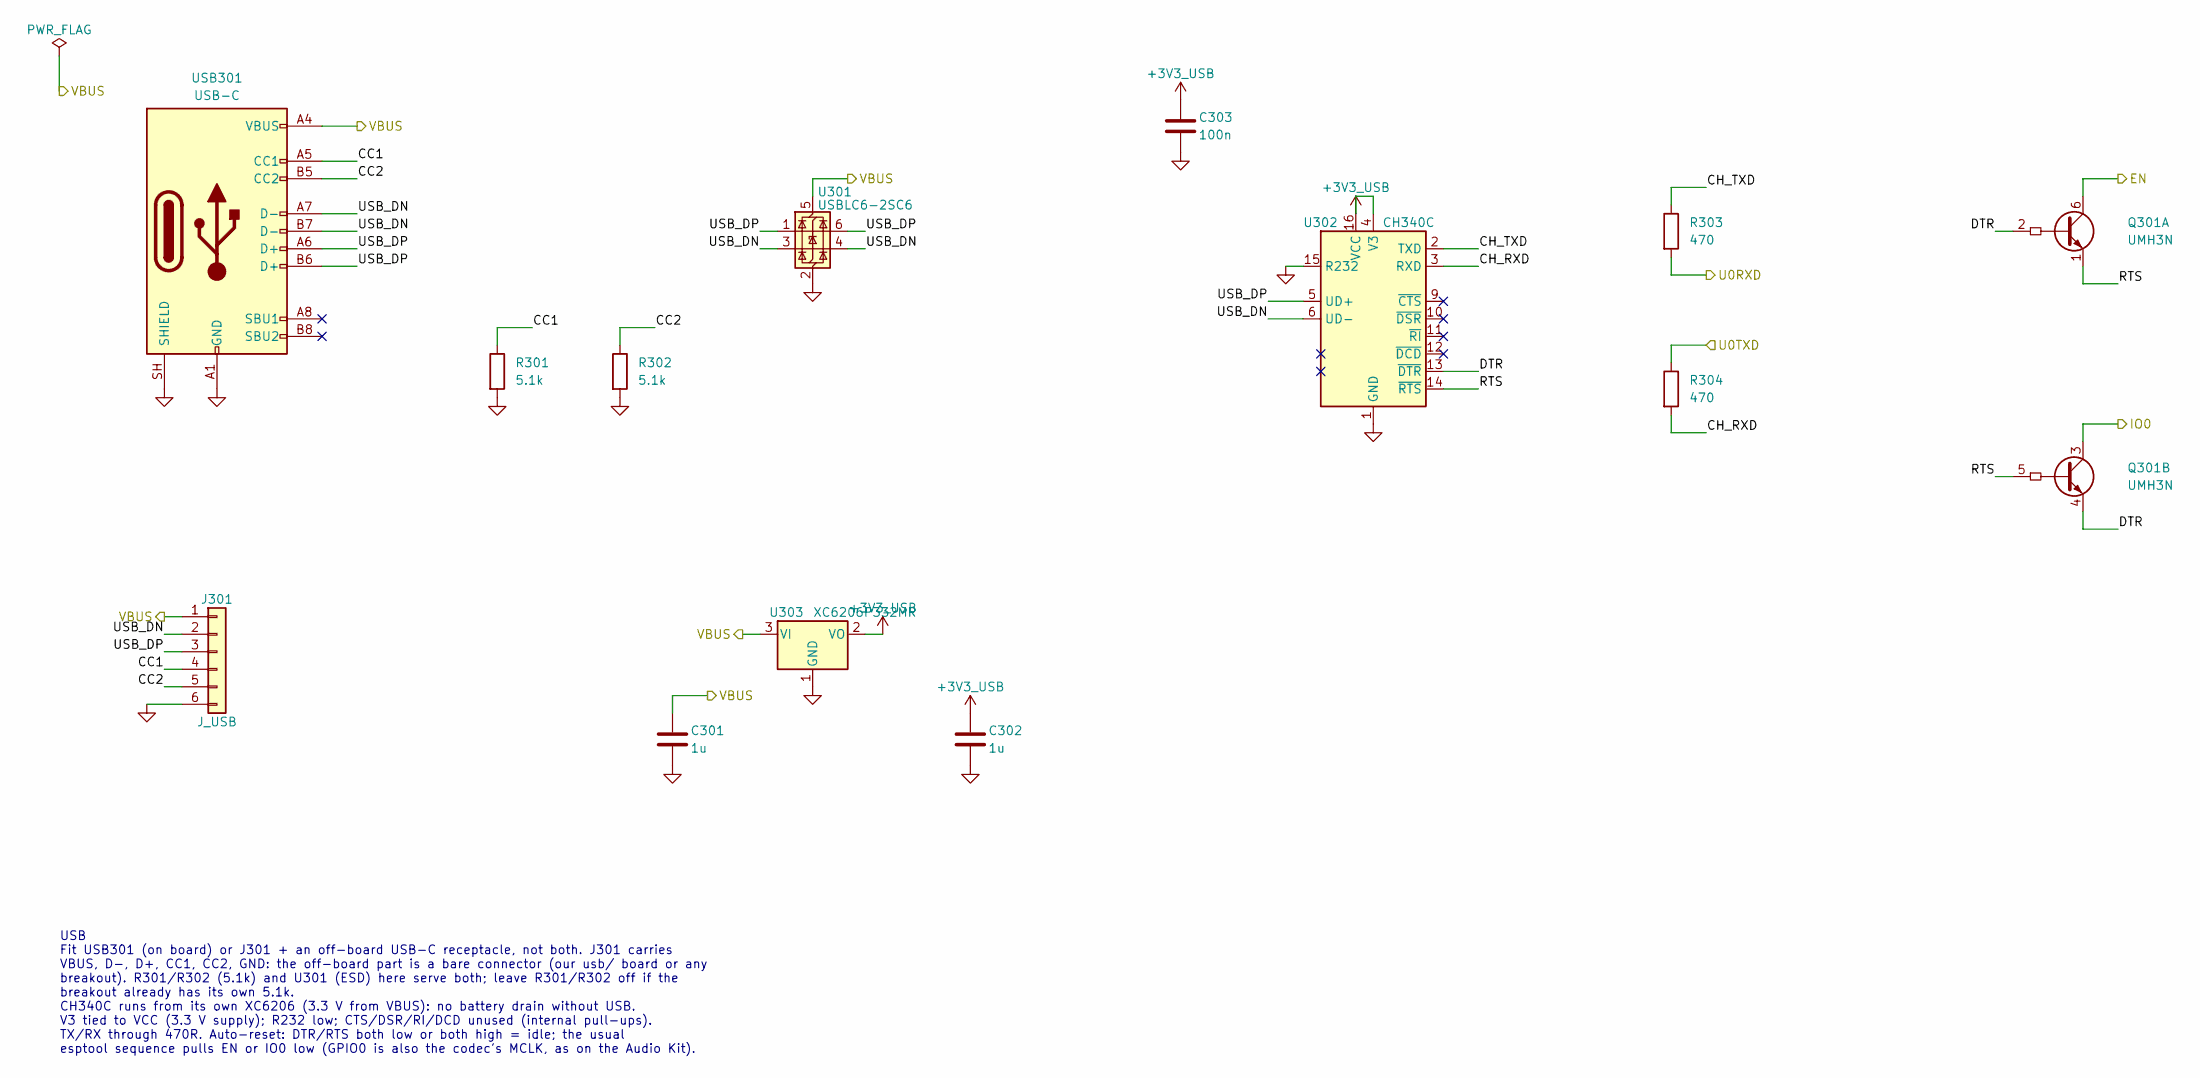
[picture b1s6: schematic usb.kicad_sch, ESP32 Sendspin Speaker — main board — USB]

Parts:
C301, C302: 1u; C_0805_2012Metric; LCSC C28323
C303: 100n; C_0805_2012Metric; LCSC C49678
J301: J_USB; JST_XH_B6B-XH-A_1x06_P2.50mm_Vertical
Q301: UMH3N; SOT-363_SC-70-6; LCSC C123008
R301, R302: 5.1k; R_0805_2012Metric; LCSC C27834
R303, R304: 470; R_0805_2012Metric; LCSC C17710
U301: USBLC6-2SC6; SOT-23-6; LCSC C7519
U302: CH340C; SOIC-16_3.9x9.9mm_P1.27mm; LCSC C84681
U303: XC6206P332MR; SOT-23-3; LCSC C5446
USB301: USB-C; USB_C_Receptacle_HRO_TYPE-C-31-M-12; LCSC C165948

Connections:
+3V3_USB: C302.1, C303.1, U302.4 (V3), U302.16 (VCC), U303.2 (VO)
/EN: Q301.6 (C1); also elsewhere on the board
/IO0: Q301.3 (C2); also elsewhere on the board
/U0RXD: R303.2; also elsewhere on the board
/U0TXD: R304.1; also elsewhere on the board
/USB/CC1: J301.4, R301.1, USB301.A5 (CC1)
/USB/CC2: J301.5, R302.1, USB301.B5 (CC2)
/USB/CH_RXD: R304.2, U302.3 (RXD)
/USB/CH_TXD: R303.1, U302.2 (TXD)
/USB/DTR: Q301.2 (B1), Q301.4 (E2), U302.13 (~DTR)
/USB/RTS: Q301.1 (E1), Q301.5 (B2), U302.14 (~RTS)
/USB/USB_DN: J301.2, U301.3 (I/O2), U301.4 (I/O2), U302.6 (UD-), USB301.A7 (D-), USB301.B7 (D-)
/USB/USB_DP: J301.3, U301.1 (I/O1), U301.6 (I/O1), U302.5 (UD+), USB301.A6 (D+), USB301.B6 (D+)
/VBUS: C301.1, J301.1, U301.5 (VBUS), U303.3 (VI), USB301.A4 (VBUS), USB301.A9 (VBUS), USB301.B4 (VBUS), USB301.B9 (VBUS); also elsewhere on the board
GND: C301.2, C302.2, C303.2, J301.6, R301.2, R302.2, U301.2 (GND), U302.1 (GND), U302.15 (R232), U303.1 (GND), USB301.A1 (GND), USB301.A12 (GND), USB301.B1 (GND), USB301.B12 (GND), USB301.SH (SHIELD); also elsewhere on the board

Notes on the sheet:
USB Fit USB301 (on board) or J301 + an off-board USB-C receptacle, not both. J301 carries VBUS, D-, D+, CC1, CC2, GND: the off-board part is a bare connector (our usb/ board or any breakout). R301/R302 (5.1k) and U301 (ESD) here serve both; leave R301/R302 off if the breakout already has its own 5.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

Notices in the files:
hardware/main/sendspin-speaker-main.kicad_pcb:
CERN-OHL-P-2.0  github.com/Boisti13/esp32-sendspin-speaker
